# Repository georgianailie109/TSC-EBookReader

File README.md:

# TSC-EBookReader

## 1. Introducere si scop

OpenBook este un dispozitiv avansat construit in jurul microcontrolerului ESP32-C6, avand mai multi senzori si interfete. Acest dispozitiv este conceput pentru a oferi o experienta de citire electronica eficienta, cu un consum redus de energie si multiple functionalitati.

---

## 2. Diagrama bloc

```
        +------------------+
        |     Baterie      |
        +--------+---------+
                 |
                 v
        +--------------------+
        | Circuit Incarcare  |
        +--------+-----------+
                 |
                 v
        +--------------------+
        |        LDO         |
        +--------+-----------+
                 |
+----------------+---------------------------+
|                |           |              |
v                v           v              v
+--------+   +-----------+  +-----------+  +----------------+
| ESP32  |<->|  Display  |<->|  BME688  |<->| Butoane tactile|
|  -C6   |   | (SPI 4W)  |   | (I2C)    |   |   (GPIO + RC)  |
+--------+   +-----------+  +-----------+  +----------------+
     |             ^            ^                ^
     |             |            |                |
     v             |      Rezistente        Circuit RC
+-----------------------+  Pull-up         debounce
|     Conector USB-C    |
+-----------------------+
```

---

## 3. Imagini

Cateva imagini din proiect (plasate in folderul `Images/`):

---

## 4. BOM (Bill of Materials)

| Componenta | Link achizitie | Link datasheet |
|-----------|----------------|----------------|
| 112A-TAAR-R03 ATTEND | https://store.comet.srl.ro/Catalogue/Product/43497/ | https://www.snapeda.com/parts/112A-TAAR-R03/Attend/datasheet/ |
| BD5229G-TR | https://www.digikey.com/en/products/detail/rohm-semiconductor/BD5229G-TR/3663792 | https://fscdn.rohm.com/en/products/databook/datasheet/ic/power/voltage_detector/bd52xxg-e.pdf |
| ESP32 WROVER BME680 Sensor | https://store.comet.srl.ro/Catalogue/Product/50164/ | https://www.bosch-sensortec.com/media/boschsensortec/downloads/datasheets/bst-bme680-ds001.pdf |
| LED CHG_LED | https://ro.mouser.com/ProductDetail/Kingbright/KP-1608SURCK?qs=2JU0tDl2GZ3FuyEWfBV1%2Fg== | https://www.snapeda.com/parts/KP-1608SURCK/Kingbright/datasheet/ |
| Condensator C0402 | https://ro.mouser.com/c/passive-components/capacitors/ceramic-capacitors/?q=CC0402 | https://componentsearchengine.com/Datasheets/2/CC0402MRX5R5BB106.pdf |
| Condensator Tant | https://ro.mouser.com/ProductDetail/KYOCERA-AVX/TAJW107M010RNJ?qs=Wtp%252Bf%2FAeVqIH8v1VxV%252B1Rg%3D%3D | https://ro.mouser.com/datasheet/2/40/TAJ-3165264.pdf |
| Q1 DMG2305UX-7 | https://www.digikey.com/en/products/detail/diodes-incorporated/DMG2305UX-7/4340666 | https://www.diodes.com/assets/Datasheets/DMG2305UX.pdf |
| RTC MODULE DS3231SN# | https://www.snapeda.com/parts/DS3231SN%23/Analog+Devices/view-part/?ref=eda | https://www.snapeda.com/parts/DS3231SN%23/Analog%20Devices/datasheet/ |
| ESP32 C6 WROOM-1-N8 | https://ro.mouser.com/ProductDetail/Espressif-Systems/ESP32-C6-WROOM-1-N8?qs=8Wlm6%252BaMh8ST02Gmwp74cw%3D%3D | https://www.snapeda.com/parts/ESP32-C6-WROOM-1-N8/Espressif%20Systems/datasheet/ |
| FH34SRJ-24S-0.5SH(99) | https://ro.mouser.com/ProductDetail/Hirose-Connector/FH34SRJ-24S-0.5SH99?qs=vcbW%252B4%252BSTIpKBl5ap9J8Fw%3D%3D | https://www.snapeda.com/parts/FH34SRJ-24S-0.5SH(99)/Hirose%20Connector/datasheet/ |
| MAX 17048G+T10 | https://www.snapeda.com/parts/MAX17048G+T10/Analog+Devices/view-part/?ref=eda | https://www.snapeda.com/parts/MAX17048G+T10/Analog%20Devices/datasheet/ |
| MBR0530 Schottky Diode | https://www.snapeda.com/parts/MBR0530/Onsemi/view-part/?ref=snap | https://www.snapeda.com/parts/MBR0530/ON%20Semiconductor/datasheet/ |
| MCP73831 Power Management | https://www.snapeda.com/parts/MCP73831T-2ACI/OT/Microchip/datasheet/ | https://www.snapeda.com/parts/MCP73831T-2ACI/OT/Microchip/datasheet/ |
| PFMF.050.1 | https://ro.mouser.com/ProductDetail/EPCOS-TDK/B72520T0350K062?qs=dEfas%2FXlABIszF52uu7vrg%3D%3D | https://www.tdk-electronics.tdk.com/inf/75/db/CTVS_14/Surge_protection_series.pdf |
| PGB1010603MR | https://www.snapeda.com/parts/PGB1010603MR/Littelfuse/view-part/?ref=eda | https://www.snapeda.com/parts/PGB1010603MR/Littelfuse%20Inc./datasheet/ |
| QWIIC_RIGHT_ANGLE CONNECTOR | https://ro.mouser.com/ProductDetail/SparkFun/PRT-14417?qs=wd5RIQLrsJhgdz%2FpmZ%2F3GQ== | https://ro.mouser.com/datasheet/2/813/Qwiic_Connector_Datasheet-1223982.pdf |
| Rezistenta R0402 | https://grabcad.com/library/resistor-0402-1) | https://www.yageo.com/upload/media/product/products/datasheet/rchip/PYu-RC_Group_51_RoHS_L_12.pdf |
| SD0805S020S1R0 | https://ro.mouser.com/ProductDetail/KYOCERA-AVX/SD0805S020S1R0?qs=jCA%252BPfw4LHbpkAoSnwrdjw%3D%3D | https://ro.mouser.com/datasheet/2/40/schottky-3165252.pdf |
| Si1308EDL-T1-GE3 MOSFET | https://www.snapeda.com/parts/SI1308EDL-T1-GE3/Vishay+Siliconix/view-part/?welcome=home&ref=eda | https://www.snapeda.com/parts/SI1308EDL-T1-GE3/Vishay%20Siliconix/datasheet/ |
| USB4110-GF-A | https://ro.mouser.com/ProductDetail/GCT/USB4110-GF-A?qs=KUoIvG%2F9IlYiZvIXQjyJeA%3D%3D | https://ro.mouser.com/datasheet/2/837/GCT_USB4110_Product_Drawing___20k_cycles-3455479.pdf |
| USBLC6-2SC6Y | https://ro.mouser.com/ProductDetail/STMicroelectronics/USBLC6-2SC6Y?qs=gNDSiZmRJS%2FOgDexvXkdow%3D%3D | https://ro.mouser.com/datasheet/2/389/usblc6_2sc6y-1852505.pdf |
| W25Q512JVEIQ | https://www.snapeda.com/parts/W25Q512JVEIQ/Winbond+Electronics/view-part/?ref=eda | https://www.winbond.com/resource-files/W25Q512JV%20SPI%20RevB%2006252019%20KMS.pdf |
| XC6220A331MR-G | https://componentsearchengine.com/part-view/XC6220A331MR-G/Torex | https://product.torexsemi.com/system/files/series/xc6220.pdf |
| 744043680 BOBINA | https://ro.mouser.com/ProductDetail/Wurth-Elektronik/744043680?qs=PGXP4M47uW6VkZq%252BkzjrHA%3D%3D | https://www.we-online.com/components/products/datasheet/744043680.pdf |

---

## 5. Functionalitatea hardware

- ESP32-C6 este componenta principala a proiectului OpenBook, oferind conectivitate Wi-Fi 6 si Bluetooth 5.0 LE. Datorita conectivitatii wireless integrate si a numarului mare de pini GPIO, microcontrollerul permite interfatarea cu diverse componente periferice, asigurand flexibilitate si performanta ridicata.
- Afisajul e-paper este conectat la ESP32-C6 prin interfata SPI si utilizeaza driver-ul BD5229G-TR pentru a gestiona tensiunile necesare functionarii. Alimentarea afisajului este controlata prin MOSFET-uri, permitand oprirea completa a acestuia atunci cand nu este utilizat, ceea ce contribuie la eficienta energetica a dispozitivului.
- Pentru monitorizarea conditiilor de mediu, proiectul utilizeaza senzorul BME688, capabil sa masoare temperatura, umiditatea, presiunea si calitatea aerului (VOC). Acesta comunica cu ESP32-C6 prin intermediul interfetei I2C si functioneaza la o tensiune de 3.3V, oferind date precise.
- Gestionarea energiei este realizata printr-un circuit de incarcare bazat pe MCP73831, care permite incarcarea bateriei cu un curent de pana la 500mA.
- Starea bateriei este monitorizata cu modulul MAX17048G+T10, care comunica prin aceeasi interfata I2C si furnizeaza informatii detaliate despre nivelul de incarcare si starea bateriei.

---

## 6. Alocarea pinilor ESP32-C6

| Componenta         | Pini ESP32           | Interfata | Observatii                             |
|--------------------|----------------------|-----------|----------------------------------------|
| Afisaj E-Paper     | IO12, IO11, IO5, IO4 | SPI       | Control si resetare afisaj             |
| Senzor BME688      | IO8, IO10            | I2C       | Date de mediu (temperatura, umiditate) |
| Card SD            | IO7                  | SPI       | Stocare externa                         |
| Modul RTC          | IO8, IO10            | I2C       | Ceas in timp real, partajeaza I2C      |
| Serial USB         | IO16, IO17           | UART      | Programare si depanare                 |

---

## 7. Pasi de implementare

Proiectarea schemei electrice si conectarea componentelor la ESP32-C6
Realizarea layout-ului 2D si pozitionarea componentelor pe PCB
Rutarea traseelor pentru semnal si alimentare
Crearea planurilor de masa pe ambele straturi
Aplicarea regulilor pentru latimea traseelor si clearance
Pozitionarea strategica a conectorilor (ex: Qwiic, USB-C)
Adaugarea pad-urilor de test pentru depanare
Generarea modelului 3D si verificarea compatibilitatii mecanice

---

## 8. Informatii suplimentare relevante

- TP-urile au fost plasate in mod optim langa marginile placii si in apropierea componentelor esentiale pentru a permite acces facil la depanare si testare.
- Pentru diodele montate pe suprafata, dimensiunea initiala a pad-urilor era prea mica, ceea ce putea crea probleme la lipire. Dimensiunea a fost ajustata pentru a asigura o conexiune electrica fiabila si o asamblare mai usoara.
- Rutarea traseelor a fost realizata pe ambele straturi ale PCB-ului (superior si inferior), asigurand o distributie eficienta a semnalelor si a alimentarii.
- Planul de masa (GND) a fost aplicat pe ambele straturi pentru a optimiza performanta electrica.

---

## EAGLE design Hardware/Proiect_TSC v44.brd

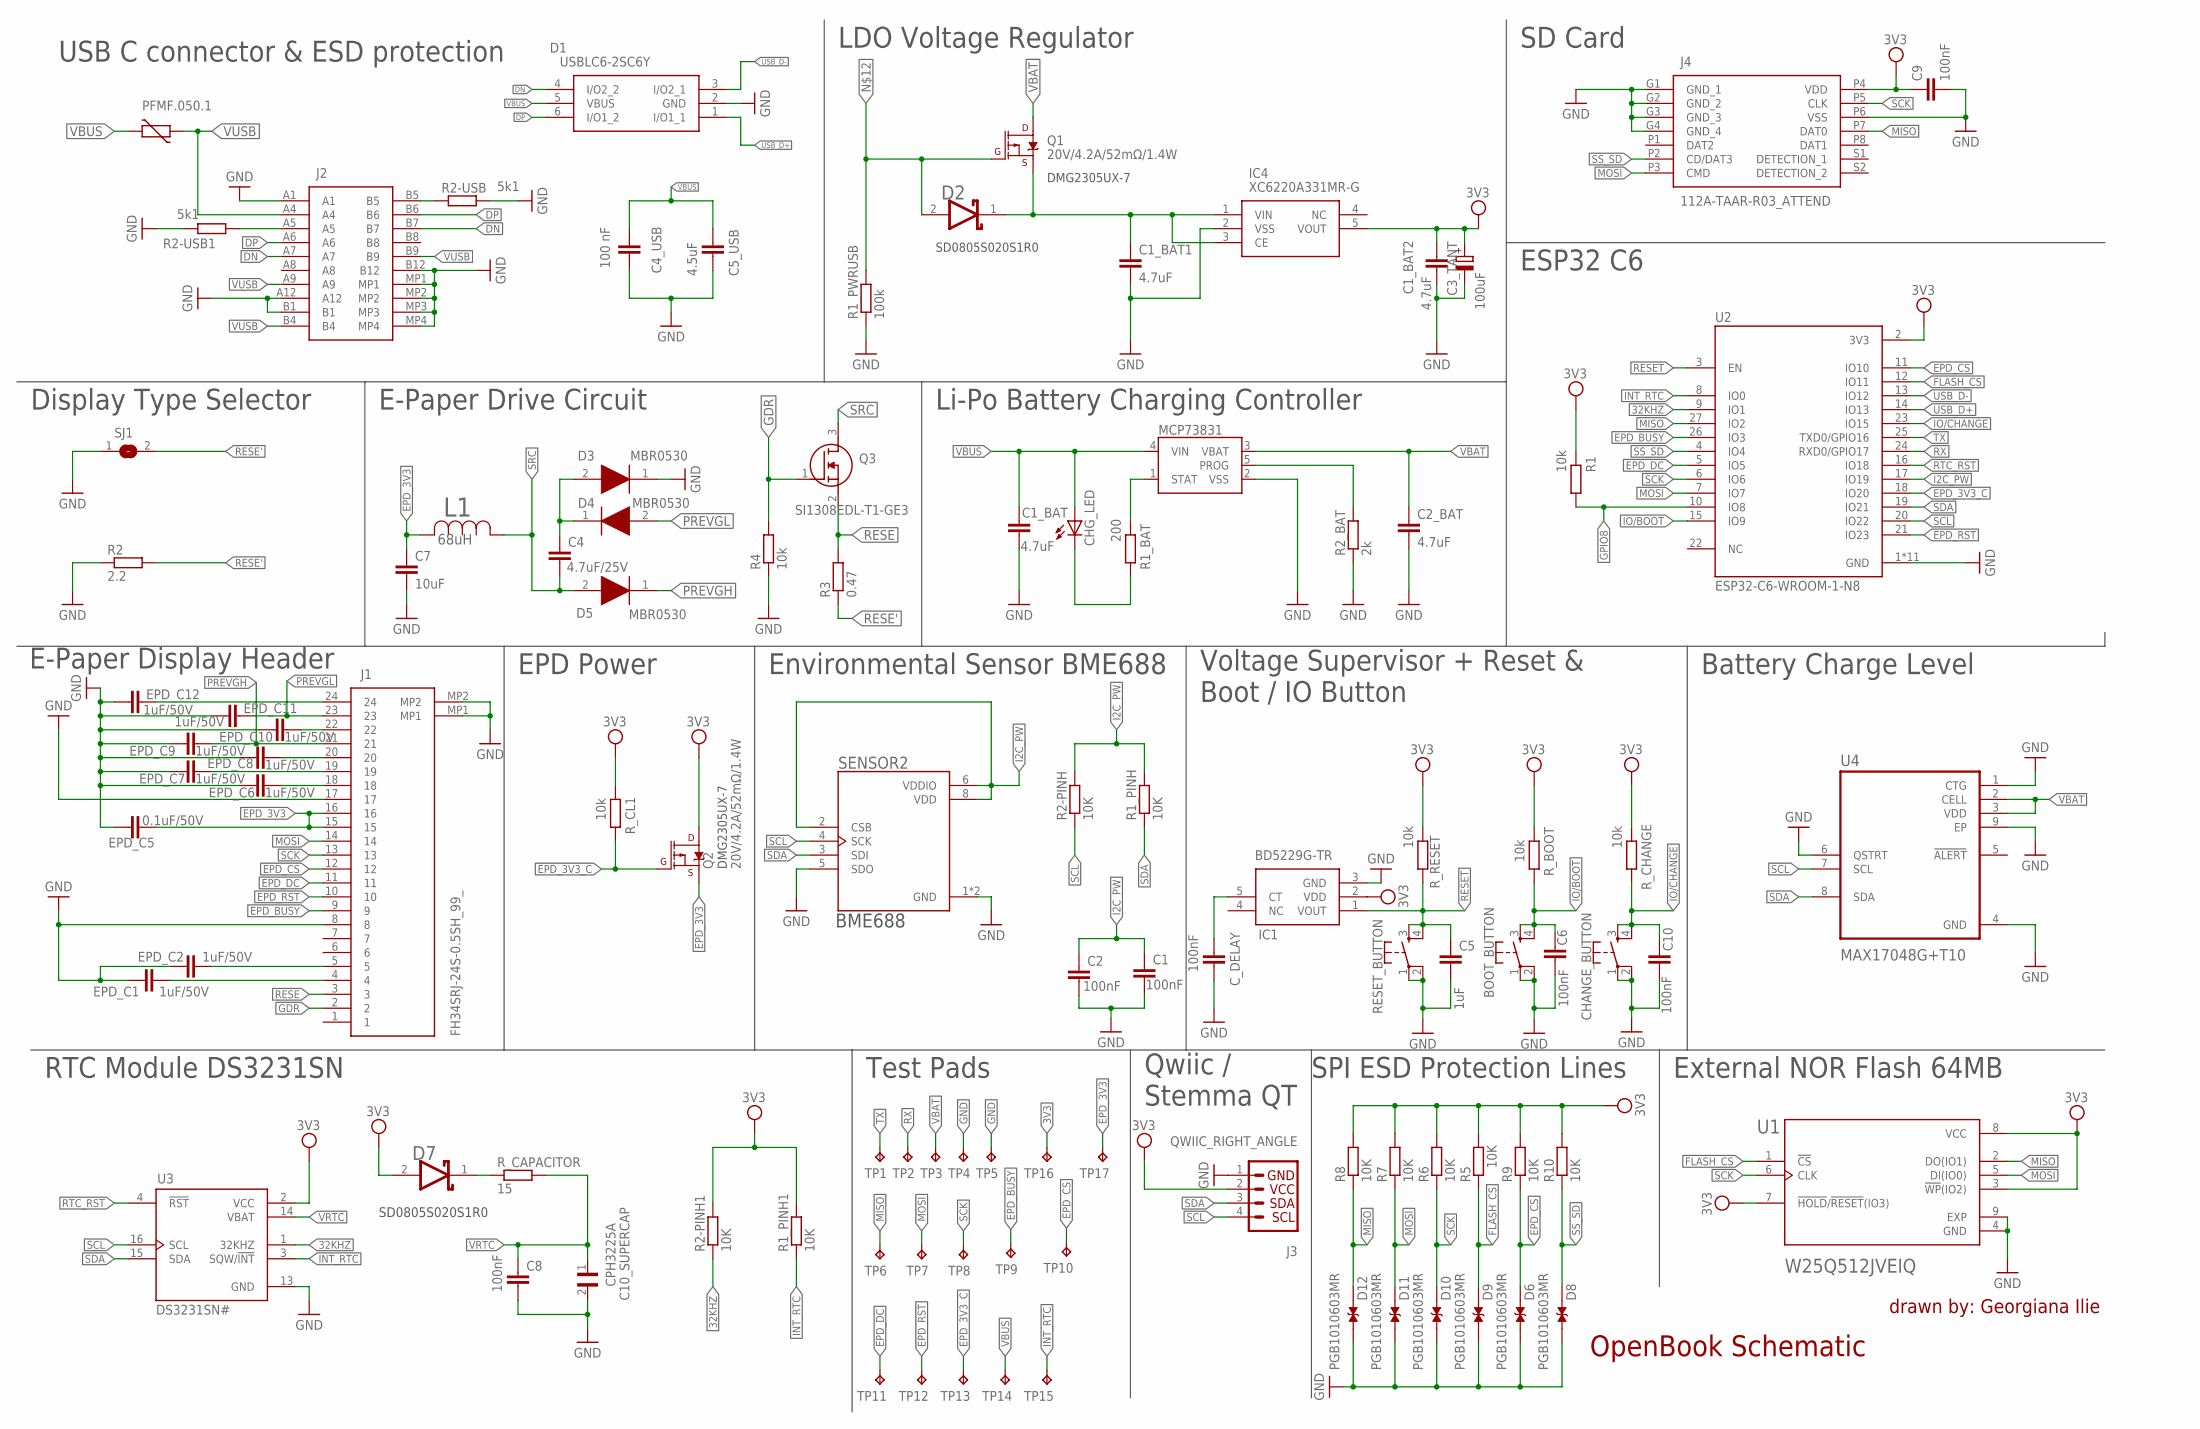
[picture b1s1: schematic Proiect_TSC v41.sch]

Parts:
BOOT_BUTTON: BUTTON_CUSYOMV1; MYBUTTON
C1, C2, C6, C8, C9, C10: 100nF; EAGLE-LTSPICE_C0402
C1_BAT, C2_BAT: 4.7uF; EAGLE-LTSPICE_C0402
C1_BAT1, C1_BAT2: 4.7uF; ESP32_WROVER_EAGLE-LTSPICE_C0402
C3_TANT: 100uF; RCL_CT3528
C4: 4.7uF/25V; EAGLE-LTSPICE_C0402
C4_USB: 100 nF; ESP32_WROVER_EAGLE-LTSPICE_C0402
C5: 1uF; EAGLE-LTSPICE_C0402
C5_USB: 4.5uF; ESP32_WROVER_EAGLE-LTSPICE_C0402
C7: 10uF; EAGLE-LTSPICE_C0402
C10_SUPERCAP: CPH3225A; CAPCP3225X100N
CHANGE_BUTTON: BUTTON_CUSYOMV1; MYBUTTON
CHG_LED: ADAFRUIT_LEDCHIP-LED0603; ADAFRUIT_CHIP-LED0603
C_DELAY: 100nF; EAGLE-LTSPICE_C0402
D1: USBLC6-2SC6Y; SOT95P280X145-6N
D2, D7: ESP32_WROVER_AVX---SD0805S020S1R0_AVX_SD0805S020S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; ESP32_WROVER_AVX---SD0805S020S1R0_AVX_SD0805S020S1R0_0
D3, D4, D5: MBR0530; SOD3716X135N
D6, D8, D9, D10, D11, D12: PGB1010603MR; DIOC1608X36N
EPD_C1, EPD_C2, EPD_C6, EPD_C7, EPD_C8, EPD_C9, EPD_C10, EPD_C11, EPD_C12: 1uF/50V; EAGLE-LTSPICE_C0402
EPD_C5: 0.1uF/50V; EAGLE-LTSPICE_C0402
IC1: BD5229G-TR; SOT95P280X125-5N
IC4: XC6220A331MR-G; SOT95P280X120-5N
J1: FH34SRJ-24S-0.5SH_99_; FH34SRJ24S05SH99
J2: SAMACSYS_PARTS_USB4110-GF-A; SAMACSYS_PARTS_USB4110GFA
J3: QWIIC_RIGHT_ANGLE; JST04_1MM_RA
J4: 112A-TAAR-R03_ATTEND; 112ATAARR03ATTEND
L1: 68uH; IND_4828-WE-TPC_WRE
MCP73831: ESP32_WROVER_SPARKFUN-IC-POWER_MCP73831; ESP32_WROVER_SPARKFUN-IC-POWER_SOT23-5
PFMF.050.1: ESP32C6_VARISTORCN1812; ESP32C6_VARISTOR_CT/CN1812
Q1, Q2: 20V/4.2A/52mΩ/1.4W; ESP32_WROVER_SPARKFUN-DISCRETESEMI_SOT23-3
Q3: SI1308EDL-T1-GE3; SOT65P210X110-3N
R1, R4: 10k; ESP32_WROVER_EAGLE-LTSPICE_R0402
R1_BAT: 200; ESP32_WROVER_EAGLE-LTSPICE_R0402
R1_PINH, R1_PINH1, R2-PINH, R2-PINH1, R5, R6, R7, R8, R9, R10: 10K; ESP32_WROVER_EAGLE-LTSPICE_R0402
R1_PWRUSB: 100k; ESP32_WROVER_EAGLE-LTSPICE_R0402
R2: 2.2; ESP32_WROVER_EAGLE-LTSPICE_R0402
R2-USB, R2-USB1: 5k1; ESP32_WROVER_EAGLE-LTSPICE_R0402
R2_BAT: 2k; ESP32_WROVER_EAGLE-LTSPICE_R0402
R3: 0.47; ESP32_WROVER_EAGLE-LTSPICE_R0402
RESET_BUTTON: BUTTON_CUSYOMV1; MYBUTTON
R_BOOT: 10k; ESP32_WROVER_EAGLE-LTSPICE_R0402
R_CAPACITOR: 15; ESP32_WROVER_EAGLE-LTSPICE_R0402
R_CHANGE: 10k; ESP32_WROVER_EAGLE-LTSPICE_R0402
R_CL1: 10k; ESP32_WROVER_EAGLE-LTSPICE_R0402
R_RESET: 10k; ESP32_WROVER_EAGLE-LTSPICE_R0402
SENSOR2: ESP32_WROVER_BME680_BME680; ESP32_WROVER_BME680_PSON80P300X300X100-8N
SJ1: SJ
TP1, TP2, TP3, TP4, TP5, TP6, TP7, TP8, TP9, TP10, TP11, TP12, TP13, TP14, TP15, TP16, TP17: TPTP20R; TP20R
U1: W25Q512JVEIQ; SON127P600X800X80-9N
U2: ESP32-C6-WROOM-1-N8; XCVR_ESP32-C6-WROOM-1-N8
U3: DS3231SN#; SOIC127P1032X265-16N
U4: MAX17048G+T10; SON50P200X200X80-9N

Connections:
3V3: C1_BAT2.1, C3_TANT.+, C9.1, D7.2 (ANODE), IC1.2 (VDD), IC4.5 (VOUT), J3.2, J4.P4 (VDD), Q2.3 (D), R1.2, R1_PINH1.2, R2-PINH1.2, R5.2, R6.2, R7.2, R8.2, R9.2, R10.2, R_BOOT.2, R_CHANGE.2, R_CL1.2, R_RESET.2, TP16.TP, U1.3 (!WP!(IO2)), U1.7 (!HOLD!/!RESET!(IO3)), U1.8 (VCC), U2.2 (3V3), U3.2 (VCC)
32KHZ: R2-PINH1.1, U2.9 (IO1), U3.1 (32KHZ)
DN: D1.4 (I/O2_2), J2.A7, J2.B7
DP: D1.6 (I/O1_2), J2.A6, J2.B6
EPD_3V3: C7.1, EPD_C5.2, J1.15, J1.16, L1.2, Q2.2 (S), TP17.TP
EPD_3V3_C: Q2.1 (G), R_CL1.1, TP13.TP, U2.18 (IO20)
EPD_BUSY: J1.9, TP9.TP, U2.26 (IO3)
EPD_CS: D6.2, J1.12, R9.1, TP10.TP, U2.11 (IO10)
EPD_DC: J1.11, TP11.TP, U2.5 (IO5)
EPD_RST: J1.10, TP12.TP, U2.21 (IO23)
FLASH_CS: D9.2, R5.1, U1.1 (!CS), U2.12 (IO11)
GDR: J1.2, Q3.1 (G), R4.2
GND: BOOT_BUTTON.1, BOOT_BUTTON.2, C1.2, C1_BAT.2, C1_BAT1.2, C1_BAT2.2, C2.2, C2_BAT.2, C3_TANT.-, C4_USB.2, C5.2, C5_USB.2, C6.2, C7.2, C8.2, C9.2, C10.2, C10_SUPERCAP.2, CHANGE_BUTTON.1, CHANGE_BUTTON.2, C_DELAY.2, D1.2 (GND), D3.1 (K), D6.1, D8.1, D9.1, D10.1, D11.1, D12.1, EPD_C1.1, EPD_C2.1, EPD_C5.1, EPD_C6.1, EPD_C7.1, EPD_C8.1, EPD_C9.1, EPD_C10.1, EPD_C11.1, EPD_C12.1, IC1.3 (GND), IC4.2 (VSS), J1.8, J1.17, J1.MP1, J1.MP2, J2.A1, J2.A12, J2.B1, J2.B12, J2.MP1, J2.MP2, J2.MP3, J2.MP4, J3.1, J4.G1 (GND_1), J4.G2 (GND_2), J4.G3 (GND_3), J4.G4 (GND_4), J4.P6 (VSS), MCP73831.2 (VSS), R1_PWRUSB.1, R2.1, R2-USB.2, R2-USB1.1, R2_BAT.1, R4.1, RESET_BUTTON.1, RESET_BUTTON.2, SENSOR2.1 (GND), SENSOR2.5 (SDO), SENSOR2.7 (GND), SJ1.1, TP4.TP, TP5.TP, U1.4 (GND), U1.9 (EXP), U2.1 (GND), U2.28 (GND), U2.29_1 (GND), U2.29_2 (GND), U2.29_3 (GND), U2.29_4 (GND), U2.29_5 (GND), U2.29_6 (GND), U2.29_7 (GND), U2.29_8 (GND), U2.29_9 (GND), U3.13 (GND), U4.1 (CTG), U4.4 (GND), U4.6 (QSTRT), U4.9 (EP)
GPIO8: R1.1, U2.10 (IO8)
I2C_PW: C1.1, C2.1, R1_PINH.2, R2-PINH.2, SENSOR2.2 (CSB), SENSOR2.6 (VDDIO), SENSOR2.8 (VDD), U2.17 (IO19)
INT_RTC: R1_PINH1.1, TP15.TP, U2.8 (IO0), U3.3 (SQW/!INT)
IO/BOOT: BOOT_BUTTON.3, BOOT_BUTTON.4, C6.1, R_BOOT.1, U2.15 (IO9)
IO/CHANGE: C10.1, CHANGE_BUTTON.3, CHANGE_BUTTON.4, R_CHANGE.1, U2.23 (IO15)
MISO: D12.2, J4.P7 (DAT0), R8.1, TP6.TP, U1.2 (DO(IO1)), U2.27 (IO2)
MOSI: D11.2, J1.14, J4.P3 (CMD), R7.1, TP7.TP, U1.5 (DI(IO0)), U2.7 (IO7)
unnamed: J2.B5, R2-USB.1
unnamed: C1_BAT1.1, D2.1 (CATHODE), IC4.1 (VIN), IC4.3 (CE), Q1.2 (S)
unnamed: J2.A5, R2-USB1.2
unnamed: C4.1, D3.2 (A), D4.1 (K)
unnamed: CHG_LED.C, R1_BAT.1
unnamed: MCP73831.1 (STAT), R1_BAT.2
unnamed: MCP73831.5 (PROG), R2_BAT.2
unnamed: EPD_C12.2, J1.24
unnamed: C_DELAY.1, IC1.5 (CT)
unnamed: D7.1 (CATHODE), R_CAPACITOR.1
unnamed: EPD_C8.2, J1.20
unnamed: D2.2 (ANODE), Q1.1 (G), R1_PWRUSB.2
unnamed: EPD_C10.2, J1.22
unnamed: EPD_C7.2, J1.19
unnamed: EPD_C6.2, J1.18
unnamed: EPD_C1.2, J1.4
unnamed: EPD_C2.2, J1.5
PREVGH: D5.1 (K), EPD_C9.2, J1.21
PREVGL: D4.2 (A), EPD_C11.2, J1.23
RESE: J1.3, Q3.2 (S), R3.2
RESE': R2.2, R3.1, SJ1.2
RESET: C5.1, IC1.1 (VOUT), RESET_BUTTON.3, RESET_BUTTON.4, R_RESET.1, U2.3 (EN)
RTC_RST: U2.16 (IO18), U3.4 (!RST)
RX: TP2.TP, U2.24 (RXD0/GPIO17)
SCK: D10.2, J1.13, J4.P5 (CLK), R6.1, TP8.TP, U1.6 (CLK), U2.6 (IO6)
SCL: J3.4, R2-PINH.1, SENSOR2.4 (SCK), U2.20 (IO22), U3.16 (SCL), U4.7 (SCL)
SDA: J3.3, R1_PINH.1, SENSOR2.3 (SDI), U2.19 (IO21), U3.15 (SDA), U4.8 (SDA)
SRC: C4.2, D5.2 (A), L1.1, Q3.3 (D)
SS_SD: D8.2, J4.P2 (CD/DAT3), R10.1, U2.4 (IO4)
TX: TP1.TP, U2.25 (TXD0/GPIO16)
USB_D+: D1.1 (I/O1_1), U2.14 (IO13)
USB_D-: D1.3 (I/O2_1), U2.13 (IO12)
VBAT: C2_BAT.1, MCP73831.3 (VBAT), Q1.3 (D), TP3.TP, U4.2 (CELL), U4.3 (VDD)
VBUS: C1_BAT.1, C4_USB.1, C5_USB.1, CHG_LED.A, D1.5 (VBUS), MCP73831.4 (VIN), PFMF.050.1.2, TP14.TP
VRTC: C8.1, C10_SUPERCAP.1, R_CAPACITOR.2, U3.14 (VBAT)
VUSB: J2.A4, J2.A9, J2.B4, J2.B9, PFMF.050.1.1

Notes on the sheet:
USB C connector & ESD protection
LDO Voltage Regulator
DMG2305UX-7
SD0805S020S1R0
SD Card
Display Type Selector
E-Paper Drive Circuit
Li-Po Battery Charging Controller
ESP32 C6
E-Paper Display Header
EPD Power
Environmental Sensor BME688
BME688
Battery Charge Level
Voltage Supervisor + Reset & Boot / IO Button
RTC Module DS3231SN
Test Pads
Qwiic / Stemma QT
SPI ESD Protection Lines
External NOR Flash 64MB
OpenBook Schematic
drawn by: Georgiana Ilie

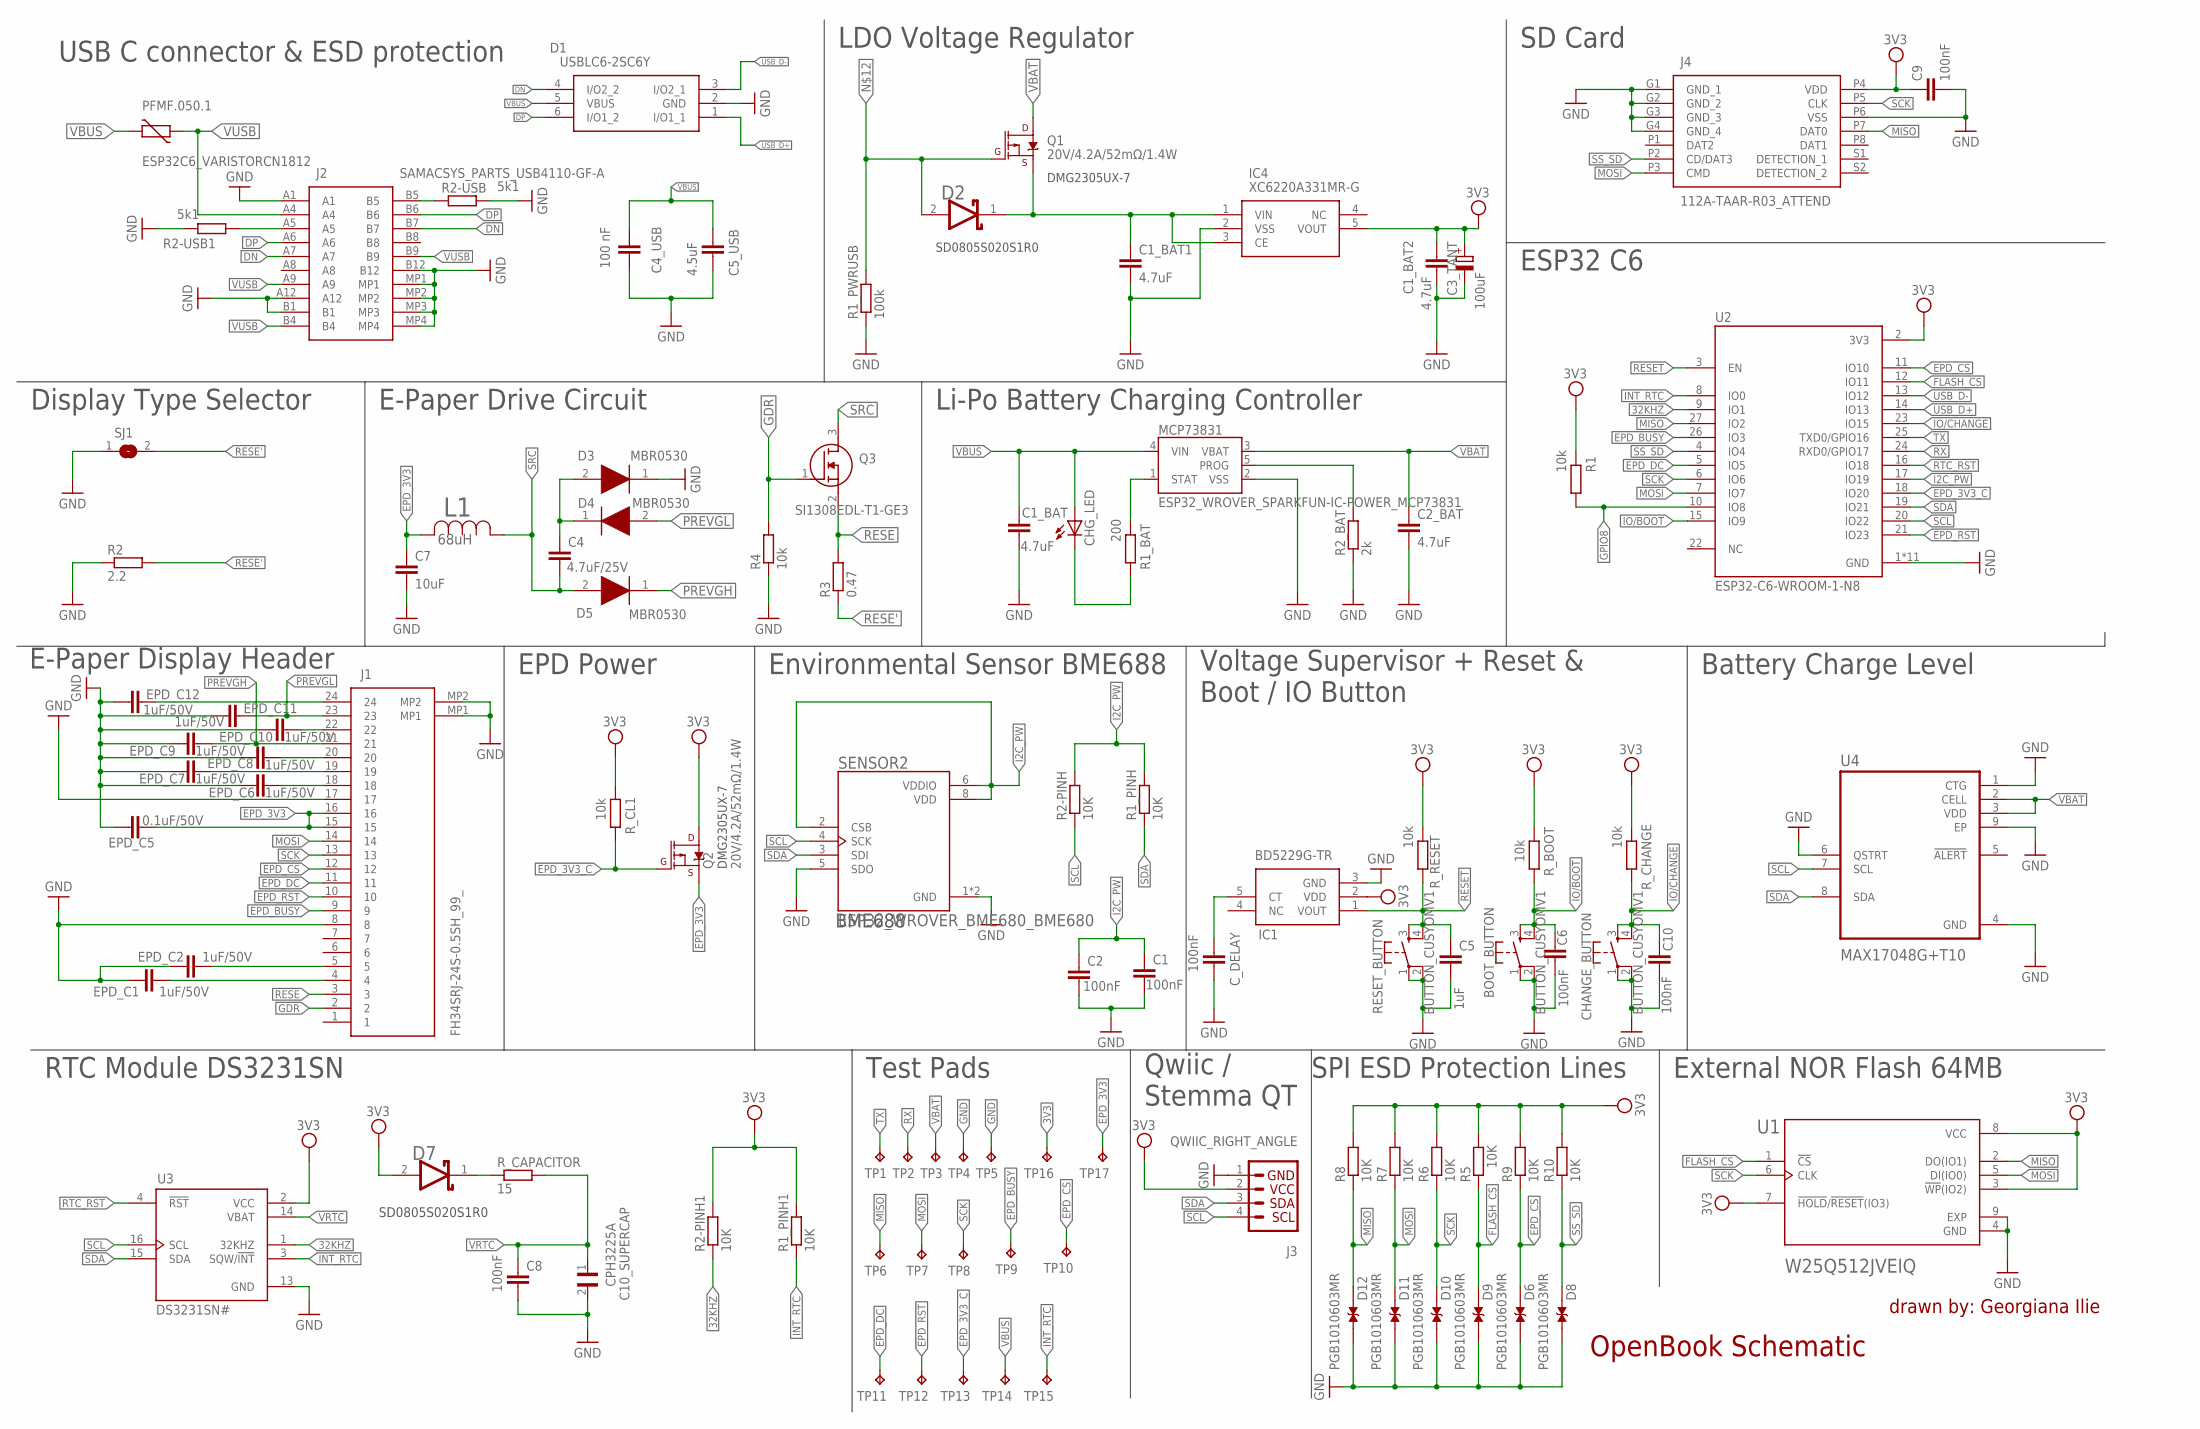
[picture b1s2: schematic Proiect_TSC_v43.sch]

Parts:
BOOT_BUTTON: BUTTON_CUSYOMV1; MYBUTTON
C1, C2, C6, C8, C9, C10: 100nF; EAGLE-LTSPICE_C0402
C1_BAT, C2_BAT: 4.7uF; EAGLE-LTSPICE_C0402
C1_BAT1, C1_BAT2: 4.7uF; ESP32_WROVER_EAGLE-LTSPICE_C0402
C3_TANT: 100uF; RCL_CT3528
C4: 4.7uF/25V; EAGLE-LTSPICE_C0402
C4_USB: 100 nF; ESP32_WROVER_EAGLE-LTSPICE_C0402
C5: 1uF; EAGLE-LTSPICE_C0402
C5_USB: 4.5uF; ESP32_WROVER_EAGLE-LTSPICE_C0402
C7: 10uF; EAGLE-LTSPICE_C0402
C10_SUPERCAP: CPH3225A; CAPCP3225X100N
CHANGE_BUTTON: BUTTON_CUSYOMV1; MYBUTTON
CHG_LED: ADAFRUIT_LEDCHIP-LED0603; ADAFRUIT_CHIP-LED0603
C_DELAY: 100nF; EAGLE-LTSPICE_C0402
D1: USBLC6-2SC6Y; SOT95P280X145-6N
D2, D7: ESP32_WROVER_AVX---SD0805S020S1R0_AVX_SD0805S020S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; ESP32_WROVER_AVX---SD0805S020S1R0_AVX_SD0805S020S1R0_0
D3, D4, D5: MBR0530; SOD3716X135N
D6, D8, D9, D10, D11, D12: PGB1010603MR; DIOC1608X36N
EPD_C1, EPD_C2, EPD_C6, EPD_C7, EPD_C8, EPD_C9, EPD_C10, EPD_C11, EPD_C12: 1uF/50V; EAGLE-LTSPICE_C0402
EPD_C5: 0.1uF/50V; EAGLE-LTSPICE_C0402
IC1: BD5229G-TR; SOT95P280X125-5N
IC4: XC6220A331MR-G; SOT95P280X120-5N
J1: FH34SRJ-24S-0.5SH_99_; FH34SRJ24S05SH99
J2: SAMACSYS_PARTS_USB4110-GF-A; SAMACSYS_PARTS_USB4110GFA
J3: QWIIC_RIGHT_ANGLE; JST04_1MM_RA
J4: 112A-TAAR-R03_ATTEND; 112ATAARR03ATTEND
L1: 68uH; IND_4828-WE-TPC_WRE
MCP73831: ESP32_WROVER_SPARKFUN-IC-POWER_MCP73831; ESP32_WROVER_SPARKFUN-IC-POWER_SOT23-5
PFMF.050.1: ESP32C6_VARISTORCN1812; ESP32C6_VARISTOR_CT/CN1812
Q1, Q2: 20V/4.2A/52mΩ/1.4W; ESP32_WROVER_SPARKFUN-DISCRETESEMI_SOT23-3
Q3: SI1308EDL-T1-GE3; SOT65P210X110-3N
R1, R4: 10k; ESP32_WROVER_EAGLE-LTSPICE_R0402
R1_BAT: 200; ESP32_WROVER_EAGLE-LTSPICE_R0402
R1_PINH, R1_PINH1, R2-PINH, R2-PINH1, R5, R6, R7, R8, R9, R10: 10K; ESP32_WROVER_EAGLE-LTSPICE_R0402
R1_PWRUSB: 100k; ESP32_WROVER_EAGLE-LTSPICE_R0402
R2: 2.2; ESP32_WROVER_EAGLE-LTSPICE_R0402
R2-USB, R2-USB1: 5k1; ESP32_WROVER_EAGLE-LTSPICE_R0402
R2_BAT: 2k; ESP32_WROVER_EAGLE-LTSPICE_R0402
R3: 0.47; ESP32_WROVER_EAGLE-LTSPICE_R0402
RESET_BUTTON: BUTTON_CUSYOMV1; MYBUTTON
R_BOOT: 10k; ESP32_WROVER_EAGLE-LTSPICE_R0402
R_CAPACITOR: 15; ESP32_WROVER_EAGLE-LTSPICE_R0402
R_CHANGE: 10k; ESP32_WROVER_EAGLE-LTSPICE_R0402
R_CL1: 10k; ESP32_WROVER_EAGLE-LTSPICE_R0402
R_RESET: 10k; ESP32_WROVER_EAGLE-LTSPICE_R0402
SENSOR2: ESP32_WROVER_BME680_BME680; ESP32_WROVER_BME680_PSON80P300X300X100-8N
SJ1: SJ
TP1, TP2, TP3, TP4, TP5, TP6, TP7, TP8, TP9, TP10, TP11, TP12, TP13, TP14, TP15, TP16, TP17: TPTP20R; TP20R
U1: W25Q512JVEIQ; SON127P600X800X80-9N
U2: ESP32-C6-WROOM-1-N8; XCVR_ESP32-C6-WROOM-1-N8
U3: DS3231SN#; SOIC127P1032X265-16N
U4: MAX17048G+T10; SON50P200X200X80-9N

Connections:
3V3: C1_BAT2.1, C3_TANT.+, C9.1, D7.2 (ANODE), IC1.2 (VDD), IC4.5 (VOUT), J3.2, J4.P4 (VDD), Q2.3 (D), R1.2, R1_PINH1.2, R2-PINH1.2, R5.2, R6.2, R7.2, R8.2, R9.2, R10.2, R_BOOT.2, R_CHANGE.2, R_CL1.2, R_RESET.2, TP16.TP, U1.3 (!WP!(IO2)), U1.7 (!HOLD!/!RESET!(IO3)), U1.8 (VCC), U2.2 (3V3), U3.2 (VCC)
32KHZ: R2-PINH1.1, U2.9 (IO1), U3.1 (32KHZ)
DN: D1.4 (I/O2_2), J2.A7, J2.B7
DP: D1.6 (I/O1_2), J2.A6, J2.B6
EPD_3V3: C7.1, EPD_C5.2, J1.15, J1.16, L1.2, Q2.2 (S), TP17.TP
EPD_3V3_C: Q2.1 (G), R_CL1.1, TP13.TP, U2.18 (IO20)
EPD_BUSY: J1.9, TP9.TP, U2.26 (IO3)
EPD_CS: D6.2, J1.12, R9.1, TP10.TP, U2.11 (IO10)
EPD_DC: J1.11, TP11.TP, U2.5 (IO5)
EPD_RST: J1.10, TP12.TP, U2.21 (IO23)
FLASH_CS: D9.2, R5.1, U1.1 (!CS), U2.12 (IO11)
GDR: J1.2, Q3.1 (G), R4.2
GND: BOOT_BUTTON.1, BOOT_BUTTON.2, C1.2, C1_BAT.2, C1_BAT1.2, C1_BAT2.2, C2.2, C2_BAT.2, C3_TANT.-, C4_USB.2, C5.2, C5_USB.2, C6.2, C7.2, C8.2, C9.2, C10.2, C10_SUPERCAP.2, CHANGE_BUTTON.1, CHANGE_BUTTON.2, C_DELAY.2, D1.2 (GND), D3.1 (K), D6.1, D8.1, D9.1, D10.1, D11.1, D12.1, EPD_C1.1, EPD_C2.1, EPD_C5.1, EPD_C6.1, EPD_C7.1, EPD_C8.1, EPD_C9.1, EPD_C10.1, EPD_C11.1, EPD_C12.1, IC1.3 (GND), IC4.2 (VSS), J1.8, J1.17, J1.MP1, J1.MP2, J2.A1, J2.A12, J2.B1, J2.B12, J2.MP1, J2.MP2, J2.MP3, J2.MP4, J3.1, J4.G1 (GND_1), J4.G2 (GND_2), J4.G3 (GND_3), J4.G4 (GND_4), J4.P6 (VSS), MCP73831.2 (VSS), R1_PWRUSB.1, R2.1, R2-USB.2, R2-USB1.1, R2_BAT.1, R4.1, RESET_BUTTON.1, RESET_BUTTON.2, SENSOR2.1 (GND), SENSOR2.5 (SDO), SENSOR2.7 (GND), SJ1.1, TP4.TP, TP5.TP, U1.4 (GND), U1.9 (EXP), U2.1 (GND), U2.28 (GND), U2.29_1 (GND), U2.29_2 (GND), U2.29_3 (GND), U2.29_4 (GND), U2.29_5 (GND), U2.29_6 (GND), U2.29_7 (GND), U2.29_8 (GND), U2.29_9 (GND), U3.13 (GND), U4.1 (CTG), U4.4 (GND), U4.6 (QSTRT), U4.9 (EP)
GPIO8: R1.1, U2.10 (IO8)
I2C_PW: C1.1, C2.1, R1_PINH.2, R2-PINH.2, SENSOR2.2 (CSB), SENSOR2.6 (VDDIO), SENSOR2.8 (VDD), U2.17 (IO19)
INT_RTC: R1_PINH1.1, TP15.TP, U2.8 (IO0), U3.3 (SQW/!INT)
IO/BOOT: BOOT_BUTTON.3, BOOT_BUTTON.4, C6.1, R_BOOT.1, U2.15 (IO9)
IO/CHANGE: C10.1, CHANGE_BUTTON.3, CHANGE_BUTTON.4, R_CHANGE.1, U2.23 (IO15)
MISO: D12.2, J4.P7 (DAT0), R8.1, TP6.TP, U1.2 (DO(IO1)), U2.27 (IO2)
MOSI: D11.2, J1.14, J4.P3 (CMD), R7.1, TP7.TP, U1.5 (DI(IO0)), U2.7 (IO7)
unnamed: J2.B5, R2-USB.1
unnamed: C1_BAT1.1, D2.1 (CATHODE), IC4.1 (VIN), IC4.3 (CE), Q1.2 (S)
unnamed: J2.A5, R2-USB1.2
unnamed: C4.1, D3.2 (A), D4.1 (K)
unnamed: CHG_LED.C, R1_BAT.1
unnamed: MCP73831.1 (STAT), R1_BAT.2
unnamed: MCP73831.5 (PROG), R2_BAT.2
unnamed: EPD_C12.2, J1.24
unnamed: C_DELAY.1, IC1.5 (CT)
unnamed: D7.1 (CATHODE), R_CAPACITOR.1
unnamed: EPD_C8.2, J1.20
unnamed: D2.2 (ANODE), Q1.1 (G), R1_PWRUSB.2
unnamed: EPD_C10.2, J1.22
unnamed: EPD_C7.2, J1.19
unnamed: EPD_C6.2, J1.18
unnamed: EPD_C1.2, J1.4
unnamed: EPD_C2.2, J1.5
PREVGH: D5.1 (K), EPD_C9.2, J1.21
PREVGL: D4.2 (A), EPD_C11.2, J1.23
RESE: J1.3, Q3.2 (S), R3.2
RESE': R2.2, R3.1, SJ1.2
RESET: C5.1, IC1.1 (VOUT), RESET_BUTTON.3, RESET_BUTTON.4, R_RESET.1, U2.3 (EN)
RTC_RST: U2.16 (IO18), U3.4 (!RST)
RX: TP2.TP, U2.24 (RXD0/GPIO17)
SCK: D10.2, J1.13, J4.P5 (CLK), R6.1, TP8.TP, U1.6 (CLK), U2.6 (IO6)
SCL: J3.4, R2-PINH.1, SENSOR2.4 (SCK), U2.20 (IO22), U3.16 (SCL), U4.7 (SCL)
SDA: J3.3, R1_PINH.1, SENSOR2.3 (SDI), U2.19 (IO21), U3.15 (SDA), U4.8 (SDA)
SRC: C4.2, D5.2 (A), L1.1, Q3.3 (D)
SS_SD: D8.2, J4.P2 (CD/DAT3), R10.1, U2.4 (IO4)
TX: TP1.TP, U2.25 (TXD0/GPIO16)
USB_D+: D1.1 (I/O1_1), U2.14 (IO13)
USB_D-: D1.3 (I/O2_1), U2.13 (IO12)
VBAT: C2_BAT.1, MCP73831.3 (VBAT), Q1.3 (D), TP3.TP, U4.2 (CELL), U4.3 (VDD)
VBUS: C1_BAT.1, C4_USB.1, C5_USB.1, CHG_LED.A, D1.5 (VBUS), MCP73831.4 (VIN), PFMF.050.1.2, TP14.TP
VRTC: C8.1, C10_SUPERCAP.1, R_CAPACITOR.2, U3.14 (VBAT)
VUSB: J2.A4, J2.A9, J2.B4, J2.B9, PFMF.050.1.1

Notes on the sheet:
USB C connector & ESD protection
LDO Voltage Regulator
DMG2305UX-7
SD0805S020S1R0
SD Card
Display Type Selector
E-Paper Drive Circuit
Li-Po Battery Charging Controller
ESP32 C6
E-Paper Display Header
EPD Power
Environmental Sensor BME688
BME688
Battery Charge Level
Voltage Supervisor + Reset & Boot / IO Button
RTC Module DS3231SN
Test Pads
Qwiic / Stemma QT
SPI ESD Protection Lines
External NOR Flash 64MB
OpenBook Schematic
drawn by: Georgiana Ilie

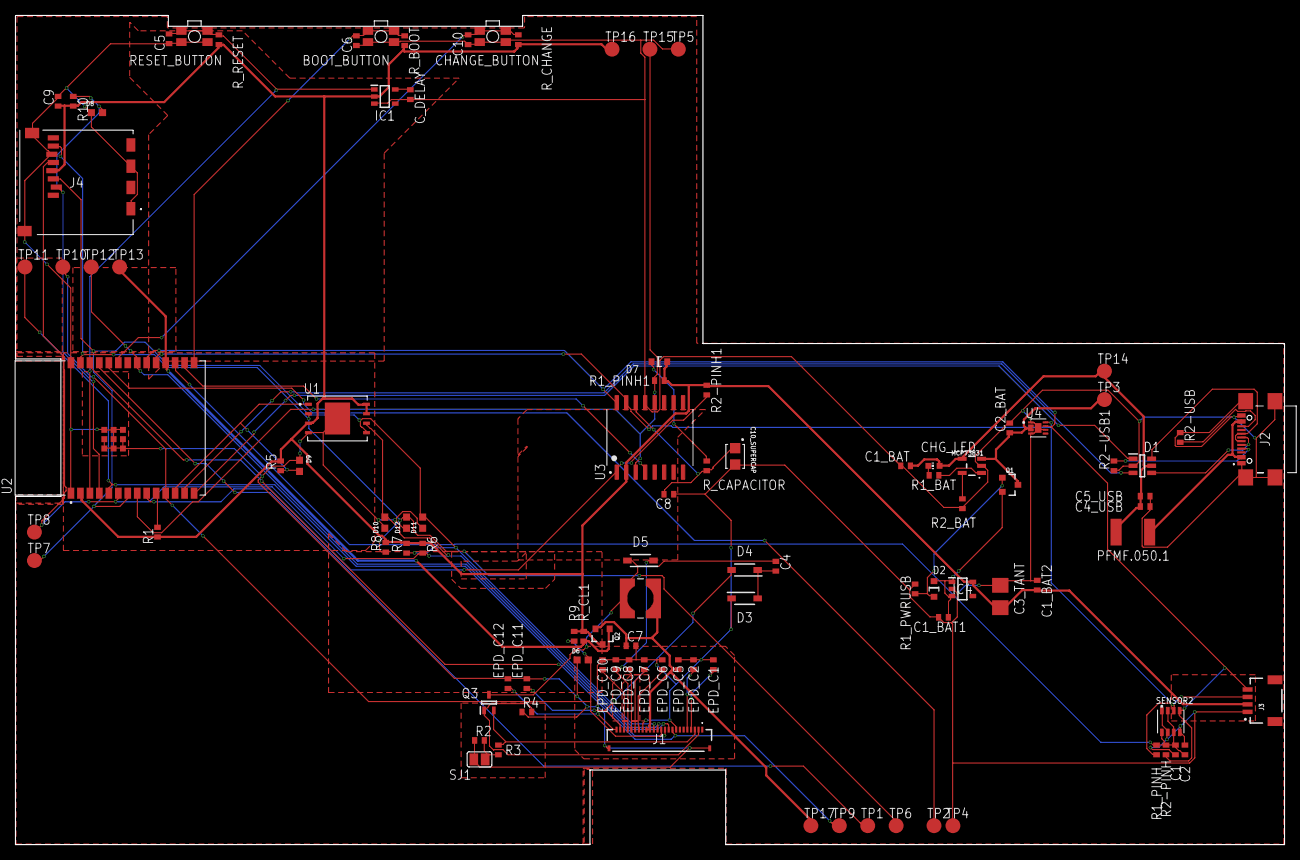
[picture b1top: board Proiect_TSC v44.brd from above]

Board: 2 copper layers, 170.2 x 111.2 mm, 103 parts (0 on the bottom side), 56 nets.

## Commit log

2025-04-06 Create LICENSE

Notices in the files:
parts and their libraries:
DeskAssistant v19 v1: COPYRIGHT: Copyright (C) 2024 Ultra Librarian. All rights reserved.
